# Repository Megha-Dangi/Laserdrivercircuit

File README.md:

# Laserdrivercircuit
KiCad schematic and LTspice simulation for laser driver circuit

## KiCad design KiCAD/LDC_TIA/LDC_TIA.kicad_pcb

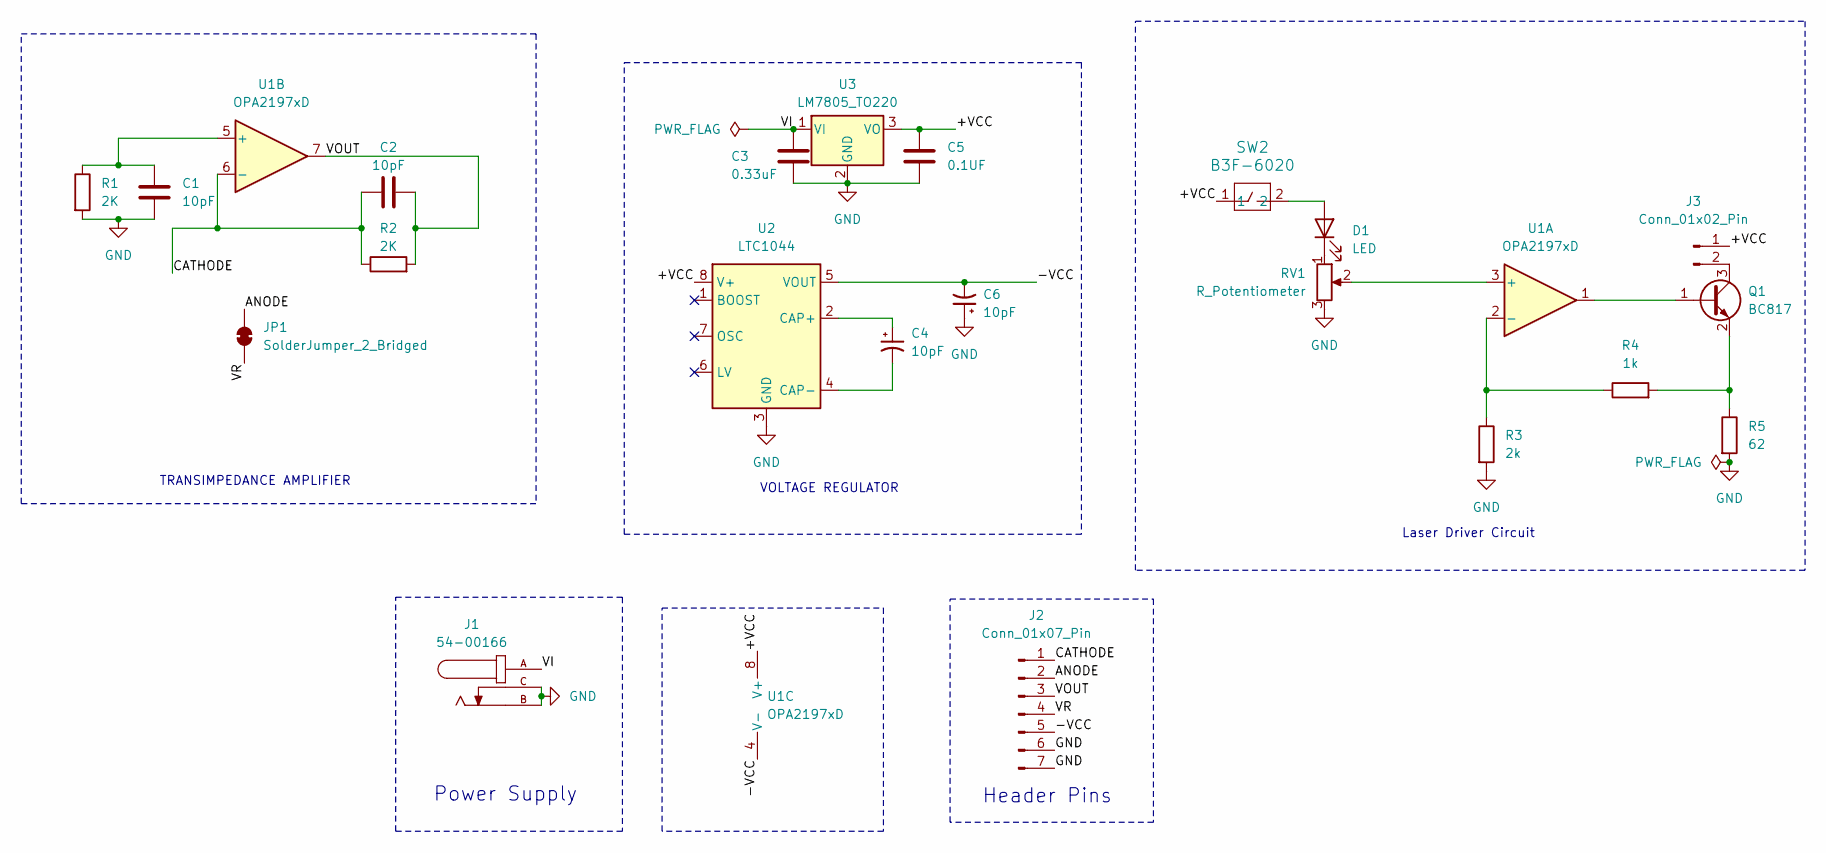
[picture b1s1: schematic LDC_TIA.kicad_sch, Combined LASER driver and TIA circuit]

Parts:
C1, C2, C4, C6: 10pF; CAPRB250W50L400T250H550
C3: 0.33uF; CAP_UEP_5X11_NCH
C5: 0.1UF; CAP_UEP_5X11_NCH
D1: LED; LED_D2.0mm_W4.8mm_H2.5mm_FlatTop
J1: 54-00166; TENSILITY_54-00166; PARTREV A
J2: Conn_01x07_Pin; PinHeader_1x07_P2.54mm_Vertical
J3: Conn_01x02_Pin; PinHeader_1x02_P2.54mm_Vertical
JP1: SolderJumper_2_Bridged; SolderJumper-2_P1.3mm_Bridged2Bar_Pad1.0x1.5mm
Q1: BC817; SOT-23
R1, R2: 2K; R_Axial_DIN0207_L6.3mm_D2.5mm_P7.62mm_Horizontal
R3: 2k; R_Axial_DIN0207_L6.3mm_D2.5mm_P7.62mm_Horizontal
R4: 1k; R_Axial_DIN0207_L6.3mm_D2.5mm_P7.62mm_Horizontal
R5: 62; RES_MRS25_VIS
RV1: R_Potentiometer; potentiometer
SW2: B3F-6020; SW_B3F-6020_OMR
U1: OPA2197xD; SOIC-8_3.9x4.9mm_P1.27mm
U2: LTC1044; PDIP-8_N_LIT
U3: LM7805_TO220; TO-220-3_Vertical

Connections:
/+VCC: C5.1, J3.1, SW2.1, U1.8 (V+), U2.8 (V+), U3.3 (VO)
/-VCC: C6.2, J2.5, U1.4 (V-), U2.5 (VOUT)
/ANODE: J2.2, JP1.2 (B)
/CATHODE: C2.1, J2.1, R2.1, U1.6 (-)
/VI: C3.1, J1.A, U3.1 (VI)
/VOUT: C2.2, J2.3, R2.2, U1.7
/VR: J2.4, JP1.1 (A)
GND: C1.2, C3.2, C5.2, C6.1, J1.B, J1.C, J2.6, J2.7, R1.2, R3.2, R5.2, RV1.3, U2.3 (GND), U3.2 (GND)
unnamed: D1.2 (A), SW2.2
unnamed: D1.1 (K), RV1.1
unnamed: J3.2, Q1.3 (C)
unnamed: Q1.1 (B), U1.1
unnamed: Q1.2 (E), R4.2, R5.1
unnamed: RV1.2, U1.3 (+)
unnamed: R3.1, R4.1, U1.2 (-)
unnamed: C1.1, R1.1, U1.5 (+)
unnamed: C4.1, U2.2 (CAP+)
unnamed: C4.2, U2.4 (CAP-)

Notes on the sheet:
VOLTAGE REGULATOR
Laser Driver Circuit
Power Supply
Header Pins
TRANSIMPEDANCE AMPLIFIER

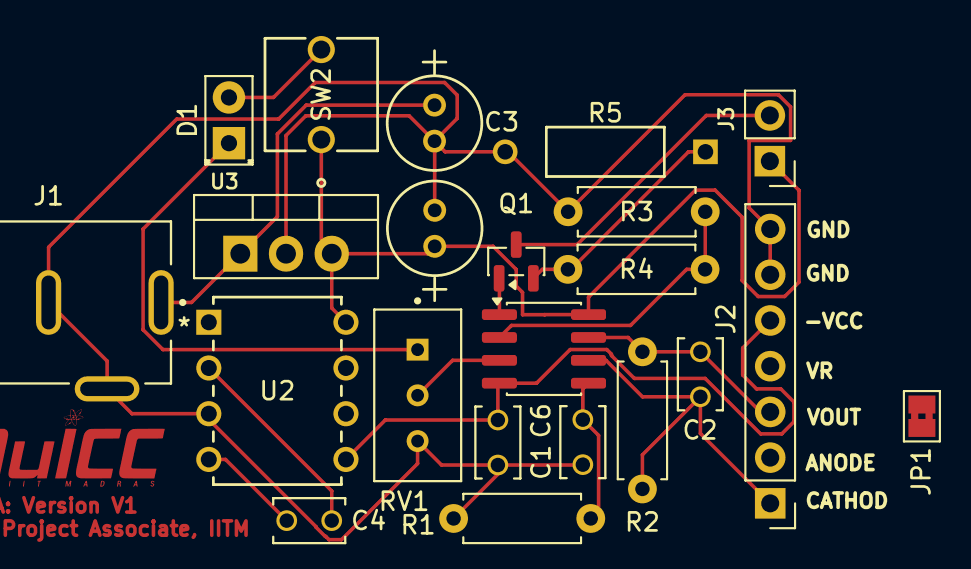
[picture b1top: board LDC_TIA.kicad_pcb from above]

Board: 2 copper layers, 22 parts (0 on the bottom side), 18 nets.

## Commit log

2025-11-03 Added KiCad schematic and LTspice simulation files
    This commit includes the main KiCad schematic for the laser driver circuit and the LTspice simulation files used for testing the photodiode response. Both files represent the initial version of the d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
2025-11-03 Added negative supply voltage section to circuit
2025-11-03 added negative regulated voltage
2025-11-04 Done with Schematics V1
2025-11-04 updated schamatics in PCB
2025-11-06 PCB layout
2025-11-07 PCB design and 3D Visualization
2025-11-10 PCB VOL 2
2025-11-10 PCB_LAYOUT_VOL2
2025-11-11 pcb v4
2025-11-11 LDC TIA SCH V3
2025-11-11 schematic v5
